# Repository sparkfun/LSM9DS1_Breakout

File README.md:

SparkFun LSM9DS1 Breakout
========================================

[*LSM9DS1 Breakout (SEN-13284)*](https://www.sparkfun.com/products/13284)

The LSM9DS1 is a versatile, motion-sensing system-in-a-chip. It houses a 3-axis accelerometer, 3-axis gyroscope, and 3-axis magnetometer – nine degrees of freedom (9DOF) in a single IC! The LSM9DS1 is equipped with a digital interface, but even that is flexible: it supports both I2C and SPI, so you’ll be hard-pressed to find a microcontroller it doesn’t work with. This IMU-in-a-chip is so cool we put it on the quarter-sized breakout board you are currently viewing!

Repository Contents
-------------------

* **/Documentation** - Data sheets, additional product information
* **/Hardware** - Eagle design files (.brd, .sch)
* **/Libraries** - Libraries for use with the LSM9DS1 Breakout
* **/Production** - Production panel files (.brd)

Documentation
--------------
* **[Library](https://github.com/sparkfun/SparkFun_LSM9DS1_Arduino_Library)** - Arduino library for the LSM9DS1 Breakout.
* **[Hookup Guide](https://learn.sparkfun.com/tutorials/lsm9ds1-breakout-hookup-guide)** - Basic hookup guide for the LSM9DS1 Breakout.
* **[SparkFun Fritzing repo](https://github.com/sparkfun/Fritzing_Parts)** - Fritzing diagrams for SparkFun products. This part can be found in the products folder.

Product Versions
----------------
* [SEN-13284](https://www.sparkfun.com/products/13284)- LSM9DS1 Breakout board

Version History
---------------
* [V_1.0.0](https://github.com/sparkfun/LSM9DS1_Breakout/releases/tag/V_1.0.0) - Initial product release repository

License Information
-------------------

This product is _**open source**_! 

Please review the LICENSE.md file for license information. 

If you have any questions or concerns on licensing, please contact techsupport@sparkfun.com.

Distributed as-is; no warranty is given.

- Your friends at SparkFun.

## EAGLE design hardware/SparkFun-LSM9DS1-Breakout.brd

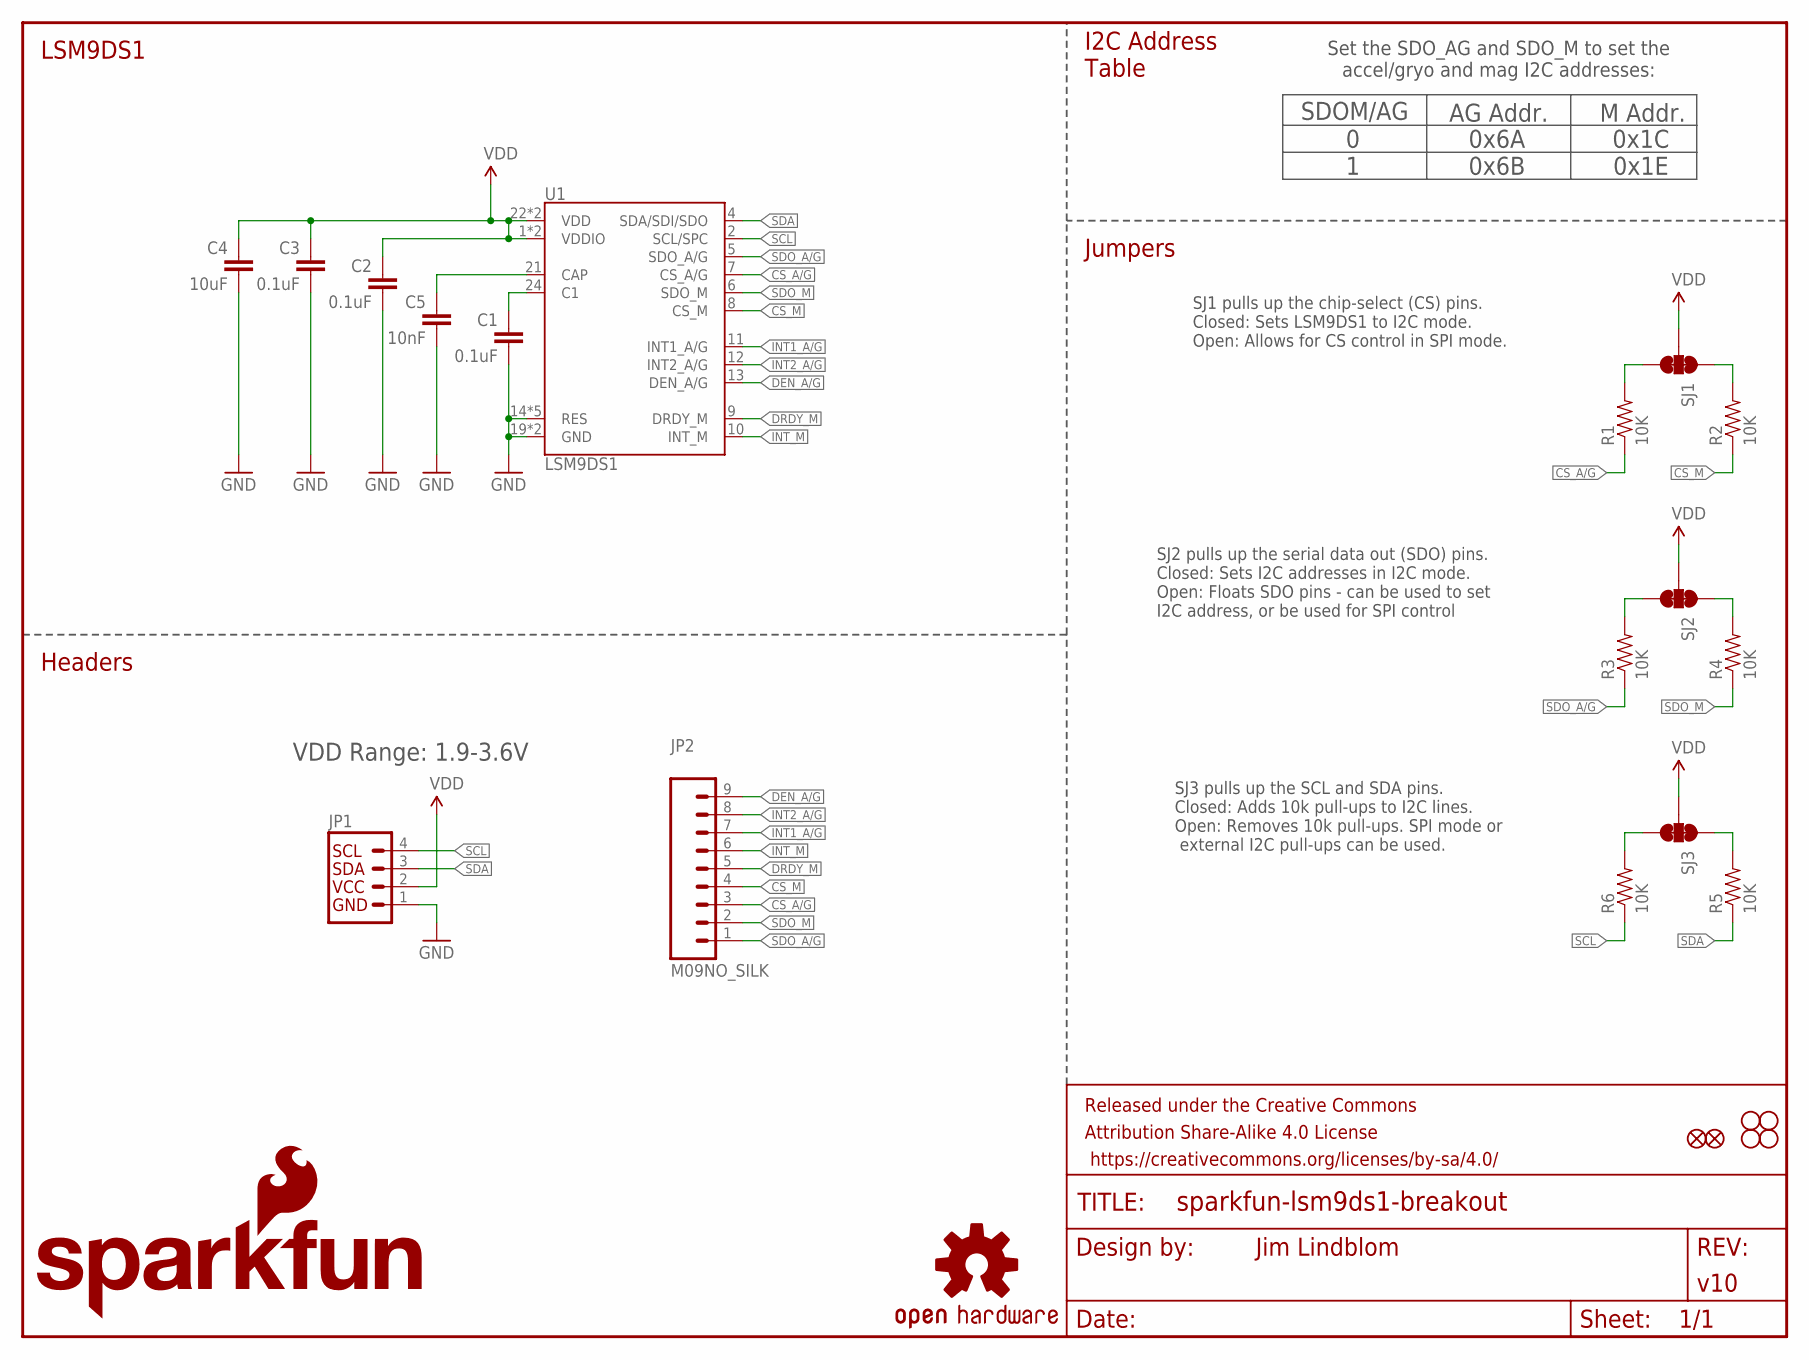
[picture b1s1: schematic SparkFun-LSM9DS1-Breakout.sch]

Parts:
C1, C2, C3: 0.1uF; 0603-CAP
C4: 10uF; 0603-CAP
C5: 10nF; 0603-CAP
FID1, FID2: FIDUCIAL1X2; FIDUCIAL-1X2
FRAME1: FRAME-LETTER; CREATIVE_COMMONS
JP1: I2C_STANDARD_NO_SILK; 1X04_NO_SILK
JP2: M09NO_SILK; 1X09_NO_SILK
LOGO1: SFE_LOGO_NAME.1_INCH; SFE_LOGO_NAME_.1
LOGO2: SFE_LOGO_FLAME.2_INCH; SFE_LOGO_FLAME_.2
LOGO3: OSHW-LOGOS; OSHW-LOGO-S
R1, R2, R3, R4, R5, R6: 10K; 0603-RES
SJ1, SJ2, SJ3: JUMPER-PAD-3-NC_BY_TRACE; PAD-JUMPER-3-3OF3_NC_BY_TRACE_YES_SILK_FULL_BOX
STANDOFF1, STANDOFF2, STANDOFF3, STANDOFF4: STAND-OFF
U1: LSM9DS1; LGA24-8X4

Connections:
C1: C1.1, U1.24 (C1)
CAP: C5.1, U1.21 (CAP)
CS_A/G: JP2.3, R1.1, U1.7 (CS_A/G)
CS_A/G_PU: R1.2, SJ1.3
CS_M: JP2.4, R2.1, U1.8 (CS_M)
CS_M_PU: R2.2, SJ1.1
DEN_A/G: JP2.9, U1.13 (DEN_A/G)
DRDY_M: JP2.5, U1.9 (DRDY_M)
GND: C1.2, C2.2, C3.2, C4.2, C5.2, JP1.1, U1.14 (RES), U1.15 (RES), U1.16 (RES), U1.17 (RES), U1.18 (RES), U1.19 (GND), U1.20 (GND)
INT1_A/G: JP2.7, U1.11 (INT1_A/G)
INT2_A/G: JP2.8, U1.12 (INT2_A/G)
INT_M: JP2.6, U1.10 (INT_M)
SCL: JP1.4, R6.1, U1.2 (SCL/SPC)
SCL_PU: R6.2, SJ3.3
SDA: JP1.3, R5.1, U1.4 (SDA/SDI/SDO)
SDA_PU: R5.2, SJ3.1
SDO_A/G: JP2.1, R3.1, U1.5 (SDO_A/G)
SDO_A/G_PU: R3.2, SJ2.3
SDO_M: JP2.2, R4.1, U1.6 (SDO_M)
SDO_M_PU: R4.2, SJ2.1
VDD: C2.1, C3.1, C4.1, JP1.2, SJ1.2, SJ2.2, SJ3.2, U1.1 (VDDIO), U1.3 (VDDIO), U1.22 (VDD), U1.23 (VDD)

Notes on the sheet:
SDOM/AG
0x1C 0x1E
AG Addr.
0 1
M Addr.
0x6A 0x6B
Set the SDO_AG and SDO_M to set the accel/gryo and mag I2C addresses:
SJ1 pulls up the chip-select (CS) pins. Closed: Sets LSM9DS1 to I2C mode. Open: Allows for CS control in SPI mode.
SJ2 pulls up the serial data out (SDO) pins. Closed: Sets I2C addresses in I2C mode. Open: Floats SDO pins - can be used to set I2C address, or be used for SPI control
SJ3 pulls up the SCL and SDA pins. Closed: Adds 10k pull-ups to I2C lines. Open: Removes 10k pull-ups. SPI mode or external I2C pull-ups can be used.
Jumpers
I2C Address Table
LSM9DS1
Headers
VDD Range: 1.9-3.6V

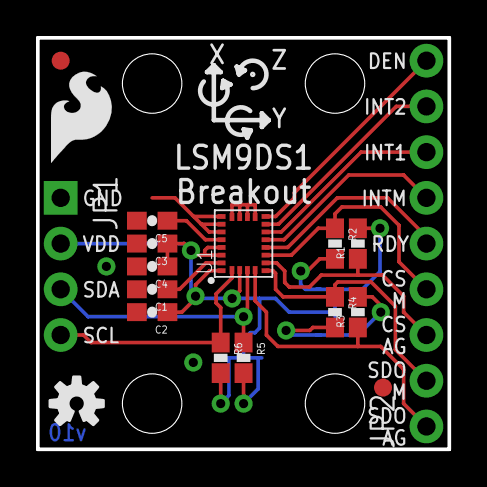
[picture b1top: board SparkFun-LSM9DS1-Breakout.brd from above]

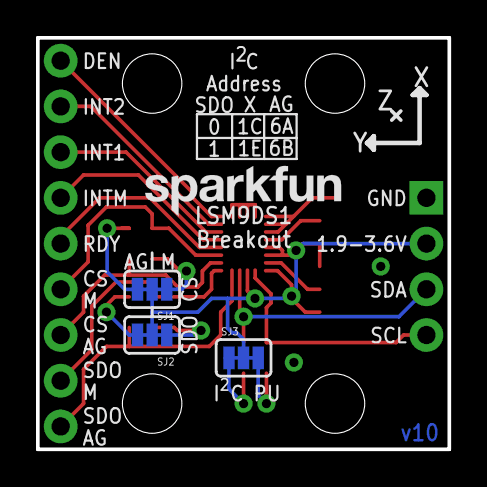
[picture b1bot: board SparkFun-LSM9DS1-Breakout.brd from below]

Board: 2 copper layers, 22.9 x 22.9 mm, 27 parts (4 on the bottom side), 21 nets.

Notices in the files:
parts and their libraries:
SparkFun-Aesthetics: Licensing: Creative Commons ShareAlike 4.0 International - https://creativecommons.org/licenses/by-sa/4.0
SparkFun-Aesthetics: Released under the Creative Commons Attribution Share-Alike 4.0 License
SparkFun-Aesthetics: https://creativecommons.org/licenses/by-sa/4.0
